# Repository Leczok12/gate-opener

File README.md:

# GATE OPENER V2

## Description

This device can open gate remotly using ESP RainMaker app or Google home.

## Files

- 3D files (case for remtoe and device)
  - [device](./case/device/)
  - [remote](./case/remote/)
- Kicad files (pcb files)
  - [ready for print pdf files](./pcb/)
  - [device](./pcb/main-board/)
  - [remote](./pcb/remote-controller-board/)
- Arduino IDE files (with software)
  - [software](./software/)

## Appearance of the device

## Shopping list

|            Name            | Amount | Url                                                             |
| :------------------------: | :----: | :-------------------------------------------------------------- |
|        ESP-WROOM32         |   1    | [Aliexpress](https://aliexpress.com/item/32808772590.html)      |
|        WS2812B LED         |   3    | [Aliexpress](https://aliexpress.com/item/4001345875756.html)    |
|    Capacitor SMD 100nf     |   3    | [Aliexpress](https://aliexpress.com/item/1005002769519482.html) |
|        USB-C 6 pin         |   1    | [Aliexpress](https://aliexpress.com/item/32966491026.html)      |
| Pin header 7 pin and 5 pin |   1    | [Aliexpress](https://aliexpress.com/item/1005005258694395.html) |
|      Pin socket 7 pin      |   1    | [Aliexpress](https://aliexpress.com/item/4001198421663.html)    |
|      Resistor 10K ohm      |   1    | -                                                               |
|           PC817            |   4    | -                                                               |
|      Resistor 100ohm       |   4    | -                                                               |
| Momentary switch 3x4x2.5mm |   3    | -                                                               |
|        AMS117 3.3V         |   1    | -                                                               |
| JST_XH_2.54 2 pin sockets  |   2    | -                                                               |
|       gate remote\*        |   1    | -                                                               |

\* in my case it is **HORMANN HSM4-868**

## Software

### Requirements

- ARDUINO IDE
  - NeoPixel
  - RainMaker

Create config.hpp file in software dir using config-template.hpp and fill gaps.

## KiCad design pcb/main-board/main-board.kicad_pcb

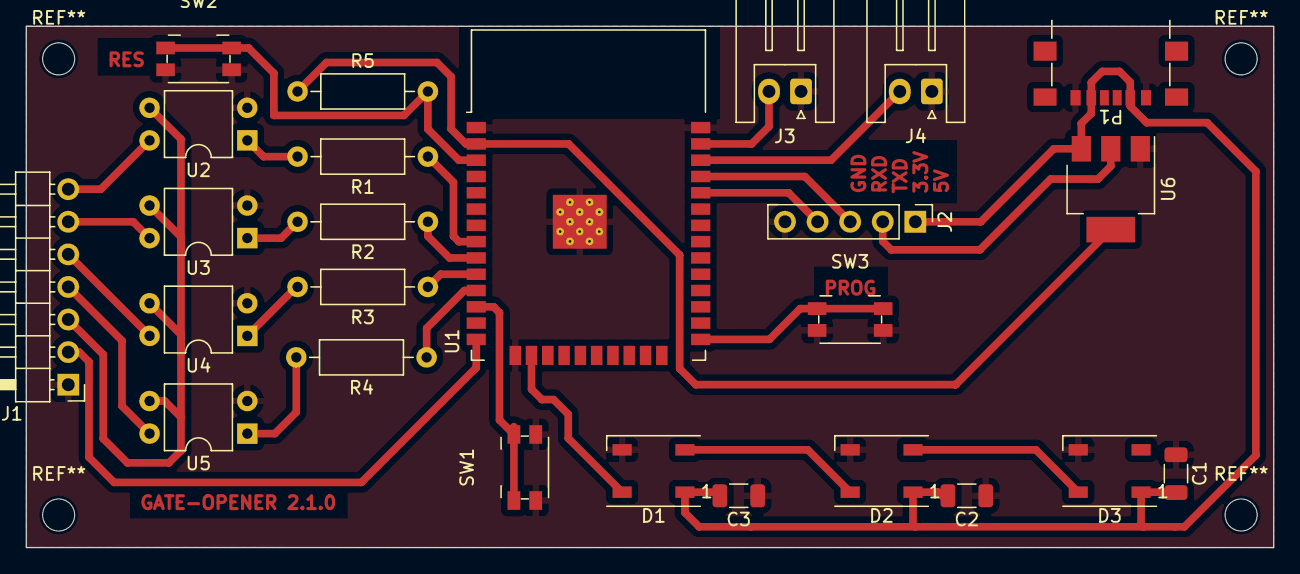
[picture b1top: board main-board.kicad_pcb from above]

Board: 2 copper layers, 97.3 x 40.6 mm, 25 parts (0 on the bottom side), 27 nets.

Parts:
C1, C2, C3: 100nF; C_1206_3216Metric
D1, D2, D3: WS2812B; LED_WS2812B_PLCC4_5.0x5.0mm_P3.2mm
J1: Conn_01x07; PinHeader_1x07_P2.54mm_Horizontal
J2: Conn_01x05; PinHeader_1x05_P2.54mm_Vertical
J3, J4: Conn_01x02; JST_XH_S2B-XH-A_1x02_P2.50mm_Horizontal
P1: USB_C_Plug_USB2.0; USB_C_Receptacle_GCT_USB4135-GF-A_6P_TopMnt_Horizontal
R1, R2, R3, R4: 100R; R_Axial_DIN0207_L6.3mm_D2.5mm_P10.16mm_Horizontal
R5: 10k; R_Axial_DIN0207_L6.3mm_D2.5mm_P10.16mm_Horizontal
SW1: SW_Push; Panasonic_EVQPUM_EVQPUD
SW2: RESET; Panasonic_EVQPUM_EVQPUD
SW3: PROG; Panasonic_EVQPUM_EVQPUD
U1: ESP32-WROOM-32
U2, U3, U4, U5: PC817; DIP-4_W7.62mm
U6: AMS1117; SOT-223-3_TabPin2

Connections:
3.3V: J2.2, R5.1, U1.2 (VDD), U6.2 (VO)
5V: C1.2, C2.2, C3.2, D1.1 (VDD), D2.1 (VDD), D3.1 (VDD), J2.1, P1.A9 (VBUS), P1.B9 (VBUS), U6.3 (VI)
EN: R5.2, SW2.1, U1.3 (EN)
GND: C1.1, C2.1, C3.1, D1.3 (VSS), D2.3 (VSS), D3.3 (VSS), J1.1, J2.5, J3.1, J4.1, P1.A12 (GND), P1.B12 (GND), SW1.2, SW2.2, SW3.2, U1.1 (GND), U1.15 (GND), U1.38 (GND), U1.39 (GND), U2.2, U3.2, U4.2, U5.2, U6.1 (ADJ)
GND2: J1.3, U2.3, U3.3, U4.3, U5.3
IO0: SW3.1, U1.25 (IO0)
IO12: J1.2, U1.14 (IO12)
IO13: D1.4 (DIN), U1.16 (IO13)
IO22: J4.2, U1.36 (IO22)
IO23: J3.2, U1.37 (IO23)
IO25: R3.1, U1.10 (IO25)
IO26: R4.1, U1.11 (IO26)
IO27: SW1.1, U1.12 (IO27)
IO32: R1.1, U1.8 (IO32)
IO33: R2.1, U1.9 (IO33)
unnamed: D1.2 (DOUT), D2.4 (DIN)
unnamed: D2.2 (DOUT), D3.4 (DIN)
unnamed: R1.2, U2.1
unnamed: R2.2, U3.1
unnamed: R3.2, U4.1
unnamed: R4.2, U5.1
RE1: J1.7, U2.4
RE2: J1.6, U3.4
RE3: J1.5, U4.4
RE4: J1.4, U5.4
RXD: J2.4, U1.34 (RXD0/IO3)
TXD: J2.3, U1.35 (TXD0/IO1)

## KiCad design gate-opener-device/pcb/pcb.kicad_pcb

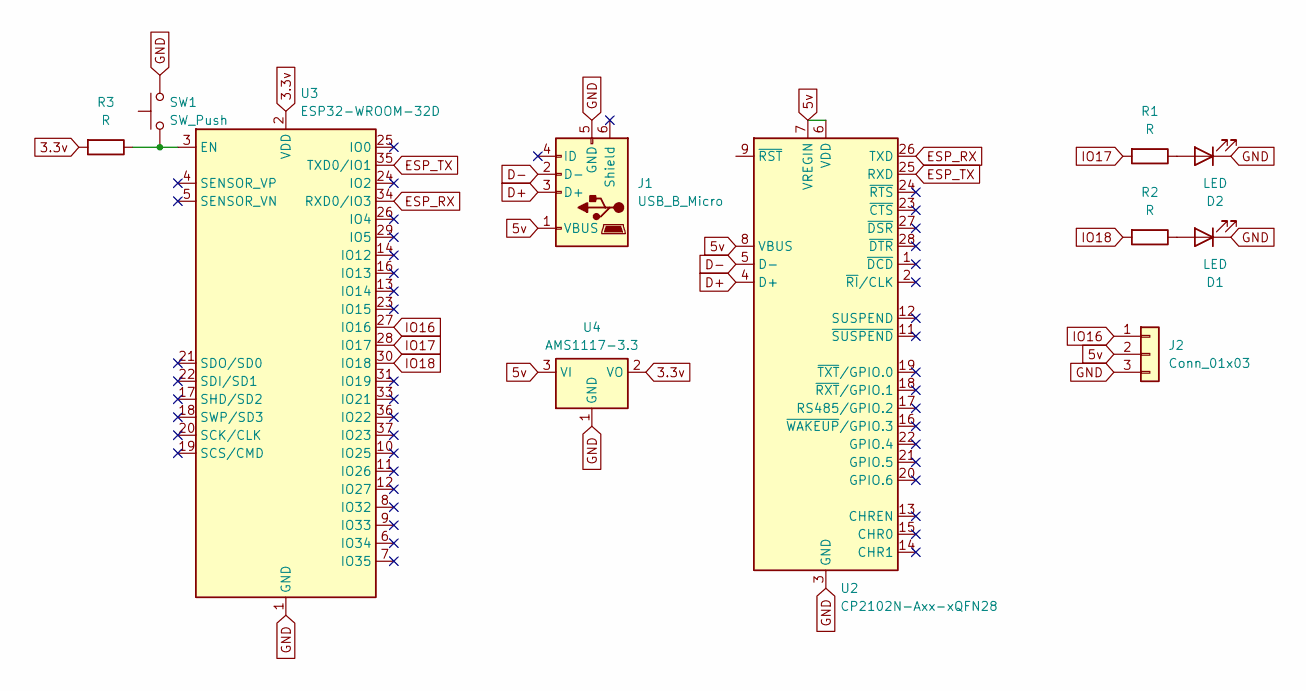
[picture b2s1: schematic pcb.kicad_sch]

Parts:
D1, D2: LED; LED_D3.0mm
J1: USB_B_Micro; USB_Micro-B_Amphenol_10103594-0001LF_Horizontal
J2: Conn_01x03; PinSocket_1x03_P2.54mm_Vertical
R1, R2, R3: R; R_Axial_DIN0309_L9.0mm_D3.2mm_P12.70mm_Horizontal
SW1: SW_Push; Panasonic_EVQPUK_EVQPUB
U2: CP2102N-Axx-xQFN28; QFN-28-1EP_5x5mm_P0.5mm_EP3.35x3.35mm
U3: ESP32-WROOM-32D
U4: AMS1117-3.3; SOT-223-3_TabPin2

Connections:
3.3v: R3.2, U3.2 (VDD), U4.2 (VO)
5v: J1.1 (VBUS), J2.2, U2.6 (VDD), U2.7 (VREGIN), U2.8 (VBUS), U4.3 (VI)
D+: J1.3 (D+), U2.4 (D+)
D-: J1.2 (D-), U2.5 (D-)
ESP_RX: U2.26 (TXD), U3.34 (RXD0/IO3)
ESP_TX: U2.25 (RXD), U3.35 (TXD0/IO1)
GND: D1.1 (K), D2.1 (K), J1.5 (GND), J2.3, SW1.2, U2.3 (GND), U2.29 (GND), U3.1 (GND), U3.15 (GND), U3.38 (GND), U3.39 (GND), U4.1 (GND)
IO16: J2.1, U3.27 (IO16)
IO17: R1.2, U3.28 (IO17)
IO18: R2.2, U3.30 (IO18)
unnamed: D1.2 (A), R2.1
unnamed: D2.2 (A), R1.1
unnamed: R3.1, SW1.1, U3.3 (EN)

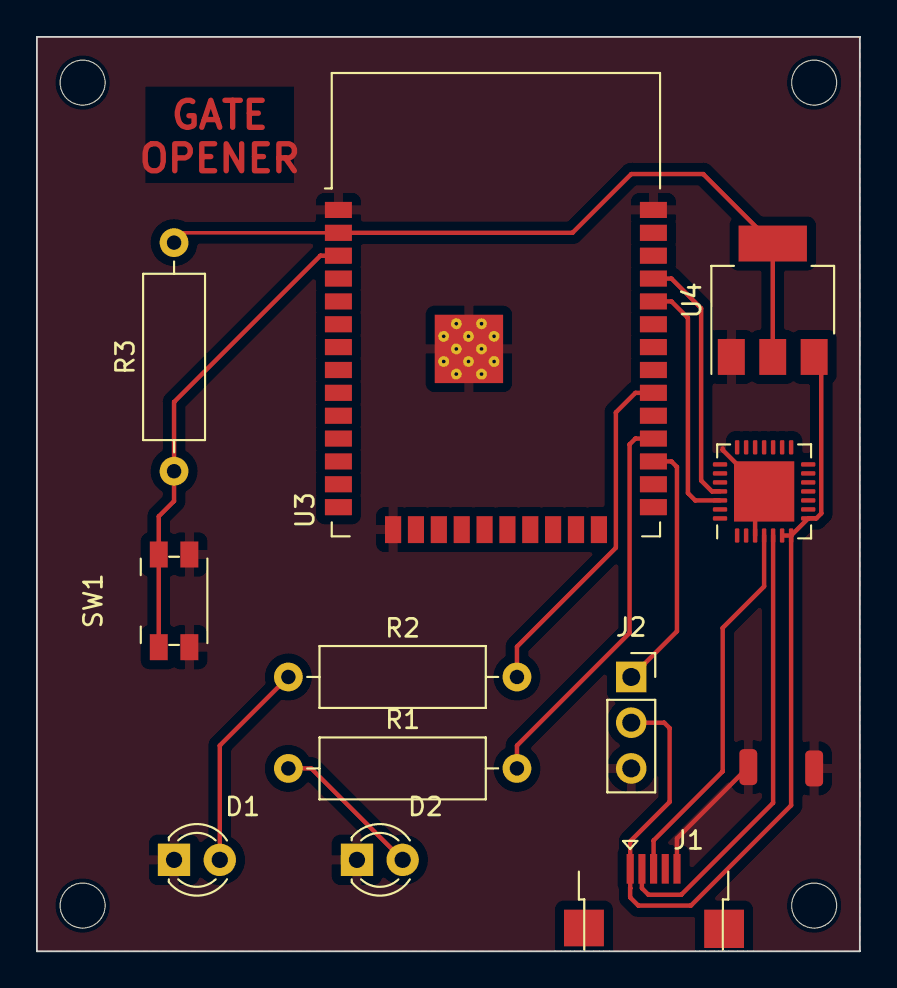
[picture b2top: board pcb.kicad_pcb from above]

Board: 2 copper layers, 45.7 x 50.8 mm, 11 parts (0 on the bottom side), 13 nets.

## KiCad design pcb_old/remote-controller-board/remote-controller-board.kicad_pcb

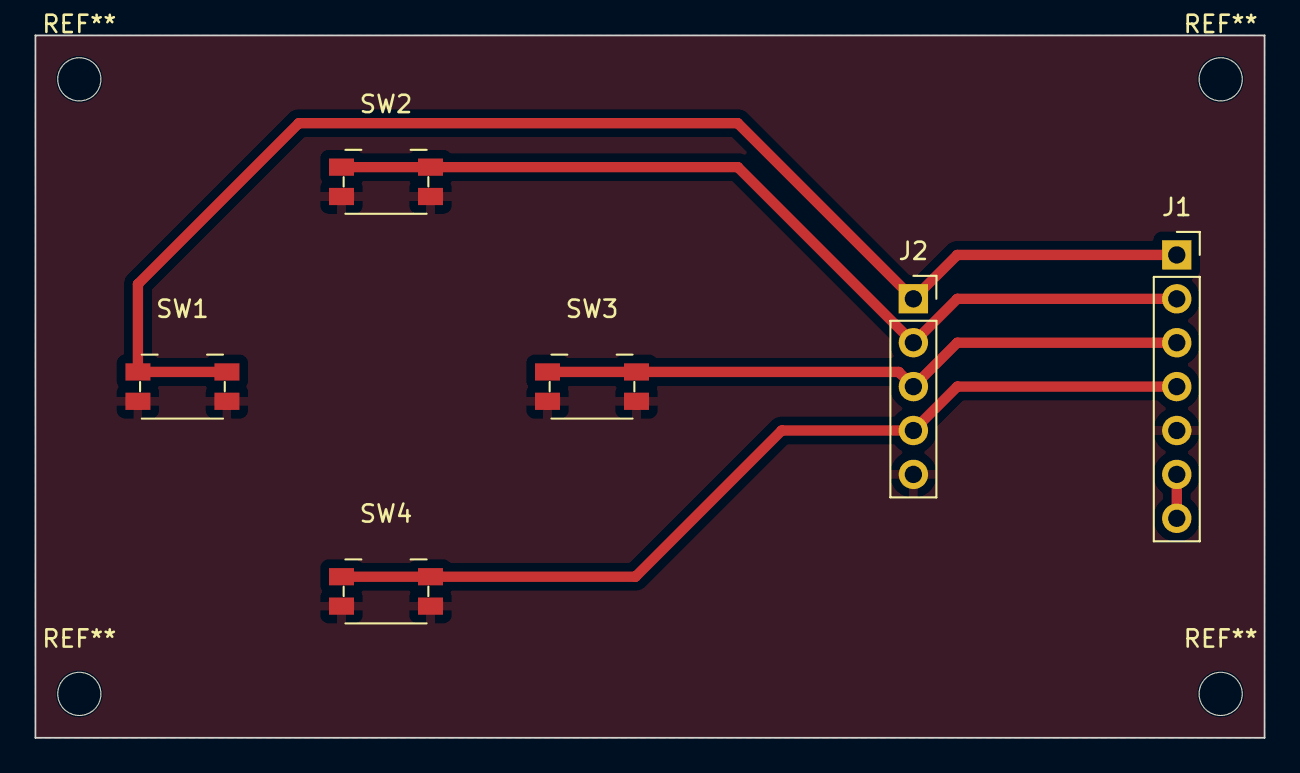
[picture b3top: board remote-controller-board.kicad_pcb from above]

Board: 2 copper layers, 71.1 x 40.6 mm, 6 parts (0 on the bottom side), 6 nets.

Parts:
J1: Conn_01x07; PinSocket_1x07_P2.54mm_Vertical
J2: Conn_01x05; PinSocket_1x05_P2.54mm_Vertical
SW1, SW2, SW3, SW4: SW_Push; Panasonic_EVQPUM_EVQPUD

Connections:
GND2: J1.5, J2.5, SW1.2, SW2.2, SW3.2, SW4.2
unnamed: J1.6, J1.7
RE1: J1.1, J2.1, SW1.1
RE2: J1.2, J2.2, SW2.1
RE3: J1.3, J2.3, SW3.1
RE4: J1.4, J2.4, SW4.1

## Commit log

2023-10-09 initial
2023-10-09 adde dredirects
2023-10-09 remopve redirects
2023-10-09 modify
2023-10-10 added new backend
2023-10-10 added start command
2023-10-10 ended api work
2023-10-11 ended app
2023-10-12 change api to ws
2023-10-12 update build command
2023-10-13 modify app for ws & disable cors in api
2023-10-15 update device
2023-10-16 modify api
2023-11-02 update case & pcb, fix connection
2023-11-03 update redme
2024-01-10 last changes for version 1
2024-01-10 init main-v2
2024-01-10 files
2024-01-10 quick fix
2024-01-22 New PCB & case
2024-01-22 created clear readme
